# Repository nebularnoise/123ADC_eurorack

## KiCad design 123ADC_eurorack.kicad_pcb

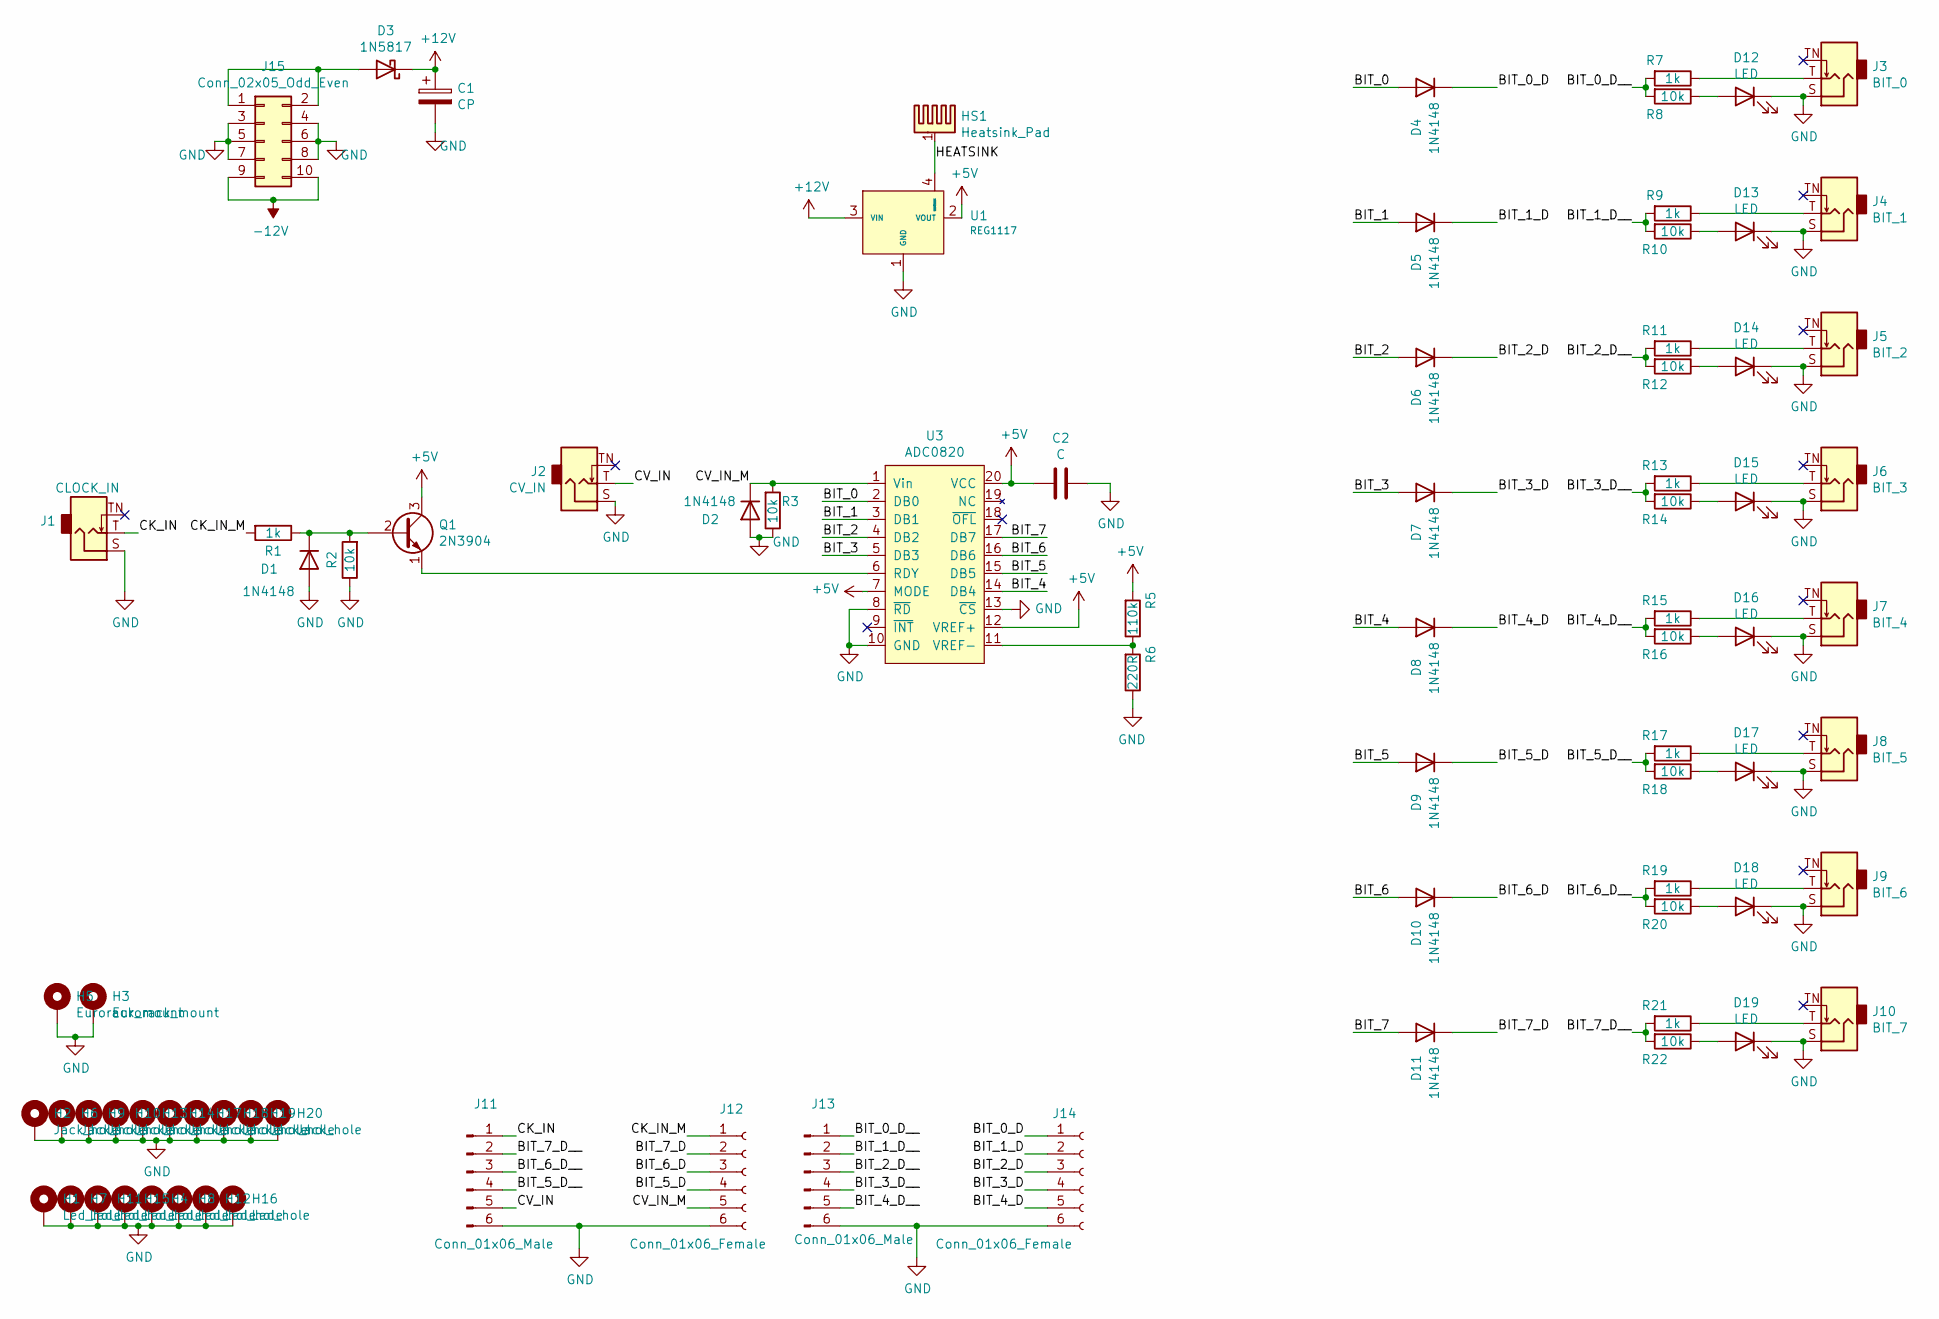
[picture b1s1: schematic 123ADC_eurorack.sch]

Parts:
C1: CP; CP_Radial_D5.0mm_P2.50mm
C2: C; C_Disc_D3.8mm_W2.6mm_P2.50mm
D1, D2, D4, D5, D6, D7, D8, D9, D10, D11: 1N4148; D_DO-35_SOD27_P7.62mm_Horizontal
D3: 1N5817; D_DO-41_SOD81_P10.16mm_Horizontal
D12, D13, D14, D15, D16, D17, D18, D19: LED; LED_D3.0mm
H1, H4, H7, H8, H11, H12, H15, H16: Led_hole; Faceplate_Hole_LED_3mm
H2, H6, H9, H10, H13, H14, H17, H18, H19, H20: Jack_hole; Faceplate_Hole_Jack_3.5mm
H3, H5: Eurorack_mount; Faceplate_Rail_Mount_Slot
HS1: Heatsink_Pad
J1: CLOCK_IN; Thonkiconn_mono
J2: CV_IN; Thonkiconn_mono
J3: BIT_0; Thonkiconn_mono
J4: BIT_1; Thonkiconn_mono
J5: BIT_2; Thonkiconn_mono
J6: BIT_3; Thonkiconn_mono
J7: BIT_4; Thonkiconn_mono
J8: BIT_5; Thonkiconn_mono
J9: BIT_6; Thonkiconn_mono
J10: BIT_7; Thonkiconn_mono
J11, J13: Conn_01x06_Male; PinHeader_1x06_P2.54mm_Vertical
J12, J14: Conn_01x06_Female; PinSocket_1x06_P2.54mm_Vertical
J15: Conn_02x05_Odd_Even; PinHeader_2x05_P2.54mm_Horizontal
Q1: 2N3904; TO-92_Inline_Wide
R1, R7, R9, R11, R13, R15, R17, R19, R21: 1k; R_Axial_DIN0207_L6.3mm_D2.5mm_P7.62mm_Horizontal
R2, R3, R8, R10, R12, R14, R16, R18, R20, R22: 10k; R_Axial_DIN0207_L6.3mm_D2.5mm_P7.62mm_Horizontal
R5: 110k; R_Axial_DIN0207_L6.3mm_D2.5mm_P7.62mm_Horizontal
R6: 220R; R_Axial_DIN0207_L6.3mm_D2.5mm_P7.62mm_Horizontal
U1: REG1117; SOT-223
U3: ADC0820; DIP-20_W7.62mm

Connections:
+5V: C2.2, Q1.3 (C), R5.2, U1.2 (VOUT), U3.7 (MODE), U3.12 (VREF+), U3.20 (VCC)
+12V: C1.1, D3.1 (K), U1.3 (VIN)
-12V: J15.9, J15.10
/BIT_0: D4.2 (A), U3.2 (DB0)
/BIT_0_D: D4.1 (K), J14.1
/BIT_0_D__: J13.1, R7.2, R8.2
/BIT_1: D5.2 (A), U3.3 (DB1)
/BIT_1_D: D5.1 (K), J14.2
/BIT_1_D__: J13.2, R9.2, R10.2
/BIT_2: D6.2 (A), U3.4 (DB2)
/BIT_2_D: D6.1 (K), J14.3
/BIT_2_D__: J13.3, R11.2, R12.2
/BIT_3: D7.2 (A), U3.5 (DB3)
/BIT_3_D: D7.1 (K), J14.4
/BIT_3_D__: J13.4, R13.2, R14.2
/BIT_4: D8.2 (A), U3.14 (DB4)
/BIT_4_D: D8.1 (K), J14.5
/BIT_4_D__: J13.5, R15.2, R16.2
/BIT_5: D9.2 (A), U3.15 (DB5)
/BIT_5_D: D9.1 (K), J12.4
/BIT_5_D__: J11.4, R17.2, R18.2
/BIT_6: D10.2 (A), U3.16 (DB6)
/BIT_6_D: D10.1 (K), J12.3
/BIT_6_D__: J11.3, R19.2, R20.2
/BIT_7: D11.2 (A), U3.17 (DB7)
/BIT_7_D: D11.1 (K), J12.2
/BIT_7_D__: J11.2, R21.2, R22.2
/CK_IN: J1.T, J11.1
/CK_IN_M: J12.1, R1.2
/CV_IN: J2.T, J11.5
/CV_IN_M: D2.1 (K), J12.5, R3.2, U3.1 (Vin)
/HEATSINK: HS1.1, U1.4 (HEATSINK)
GND: C1.2, C2.1, D1.2 (A), D2.2 (A), D12.1 (K), D13.1 (K), D14.1 (K), D15.1 (K), D16.1 (K), D17.1 (K), D18.1 (K), D19.1 (K), H1.1, H2.1, H3.1, H4.1, H5.1, H6.1, H7.1, H8.1, H9.1, H10.1, H11.1, H12.1, H13.1, H14.1, H15.1, H16.1, H17.1, H18.1, H19.1, H20.1, J1.S, J2.S, J3.S, J4.S, J5.S, J6.S, J7.S, J8.S, J9.S, J10.S, J11.6, J12.6, J13.6, J14.6, J15.3, J15.4, J15.5, J15.6, J15.7, J15.8, R2.1, R3.1, R6.1, U1.1 (GND), U3.8 (~RD), U3.10 (GND), U3.13 (~CS)
unnamed: D1.1 (K), Q1.2 (B), R1.1, R2.2
unnamed: D3.2 (A), J15.1, J15.2
unnamed: D12.2 (A), R8.1
unnamed: D13.2 (A), R10.1
unnamed: D14.2 (A), R12.1
unnamed: D15.2 (A), R14.1
unnamed: D16.2 (A), R16.1
unnamed: D17.2 (A), R18.1
unnamed: D18.2 (A), R20.1
unnamed: D19.2 (A), R22.1
unnamed: J3.T, R7.1
unnamed: J4.T, R9.1
unnamed: J5.T, R11.1
unnamed: J6.T, R13.1
unnamed: J7.T, R15.1
unnamed: J8.T, R17.1
unnamed: J9.T, R19.1
unnamed: J10.T, R21.1
unnamed: Q1.1 (E), U3.6 (RDY)
unnamed: R5.1, R6.2, U3.11 (VREF-)

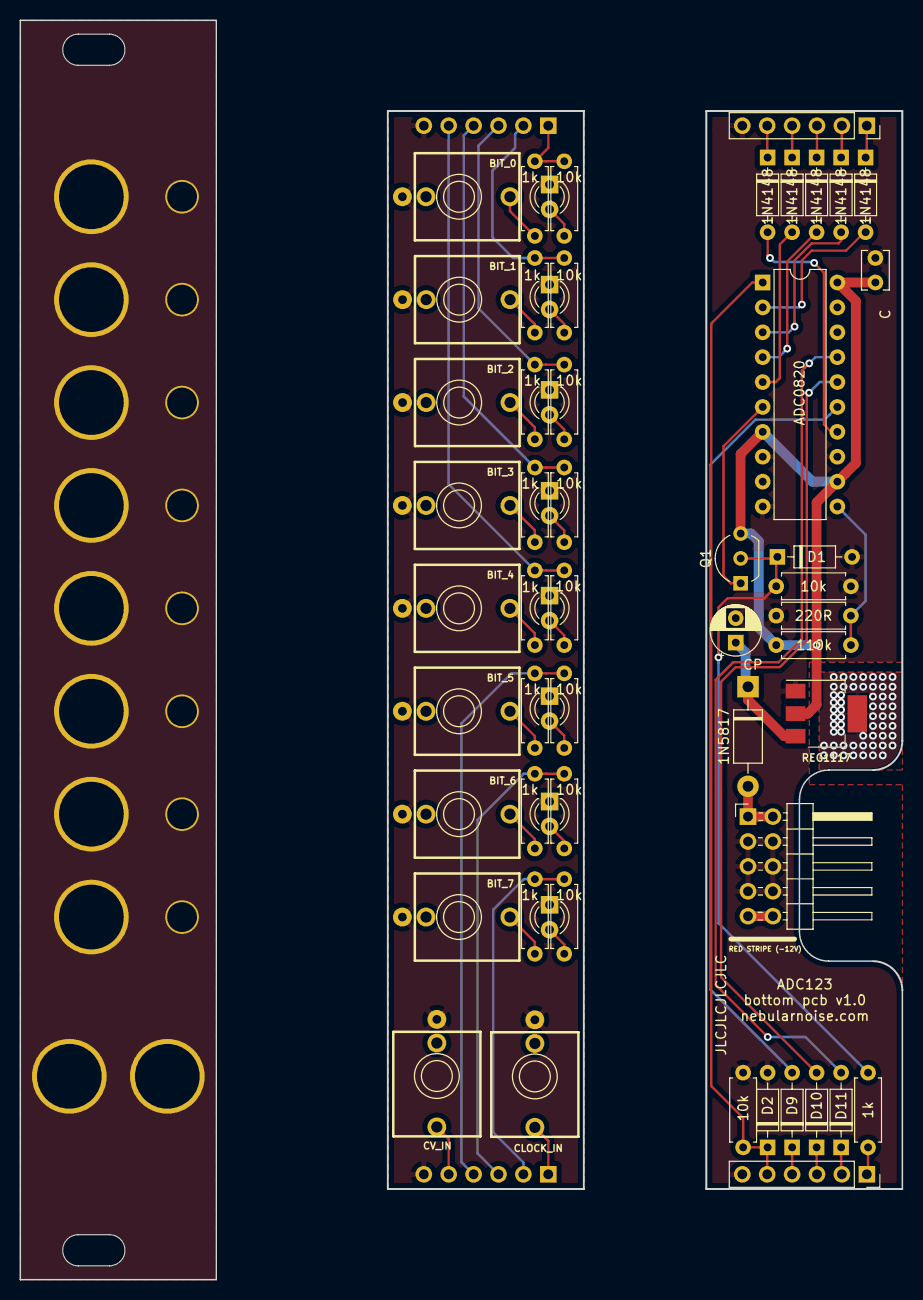
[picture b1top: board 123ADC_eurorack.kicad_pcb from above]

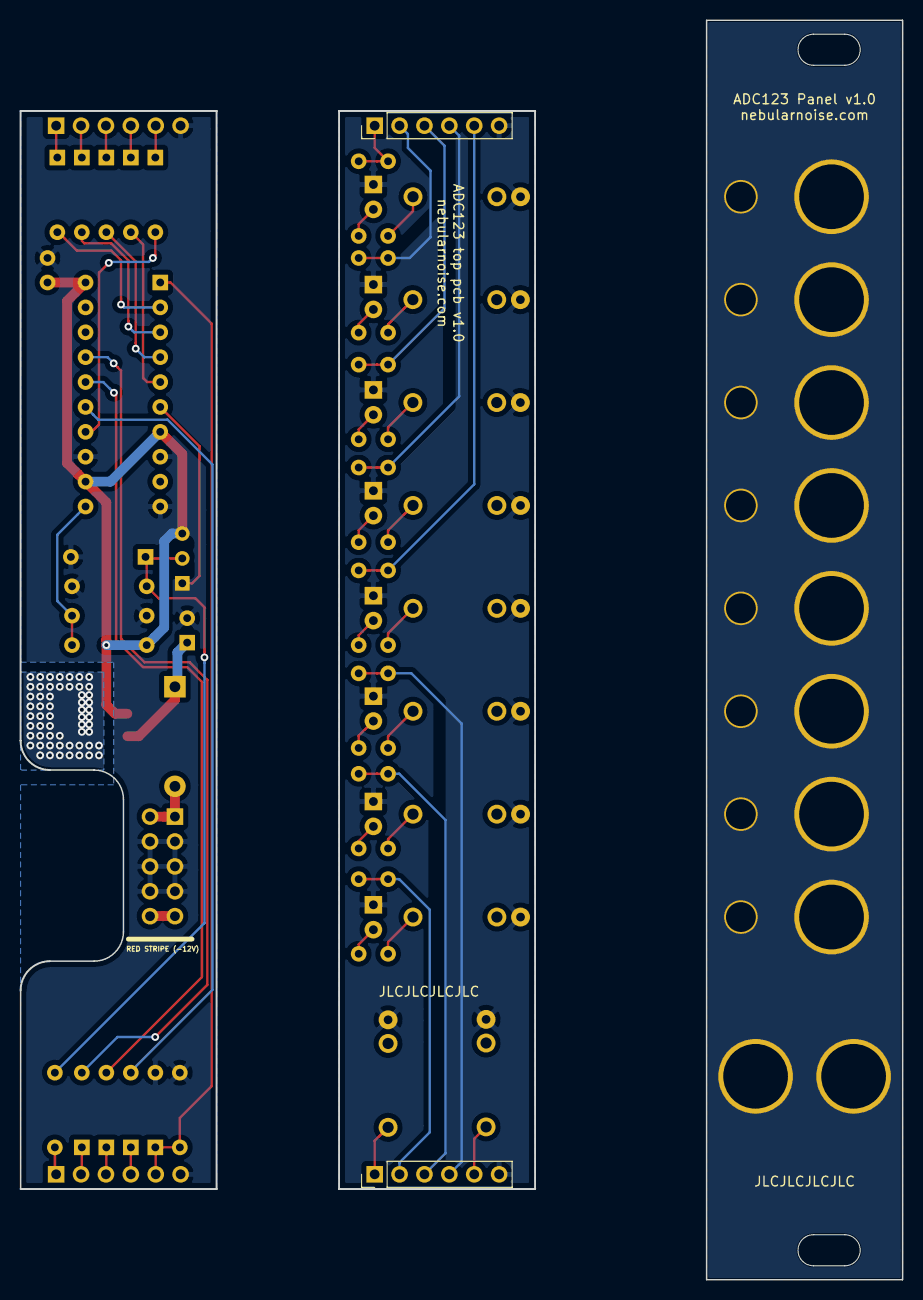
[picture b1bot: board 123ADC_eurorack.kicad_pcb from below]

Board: 2 copper layers, 90.0 x 128.4 mm, 80 parts (2 on the bottom side), 52 nets.

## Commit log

2020-01-26 :tada: First commit
2020-01-26 :sparkles: Add reverse power protection and power conditioning caps
2020-01-26 :sparkles: Add graphics for output numbers, and LMNC logo
2020-01-27 :sparkles: Name in handwriting
2020-02-19 :recycle: Clean up silkscreen
    same
2021-02-01 :bug: Fix resistor values
    same
